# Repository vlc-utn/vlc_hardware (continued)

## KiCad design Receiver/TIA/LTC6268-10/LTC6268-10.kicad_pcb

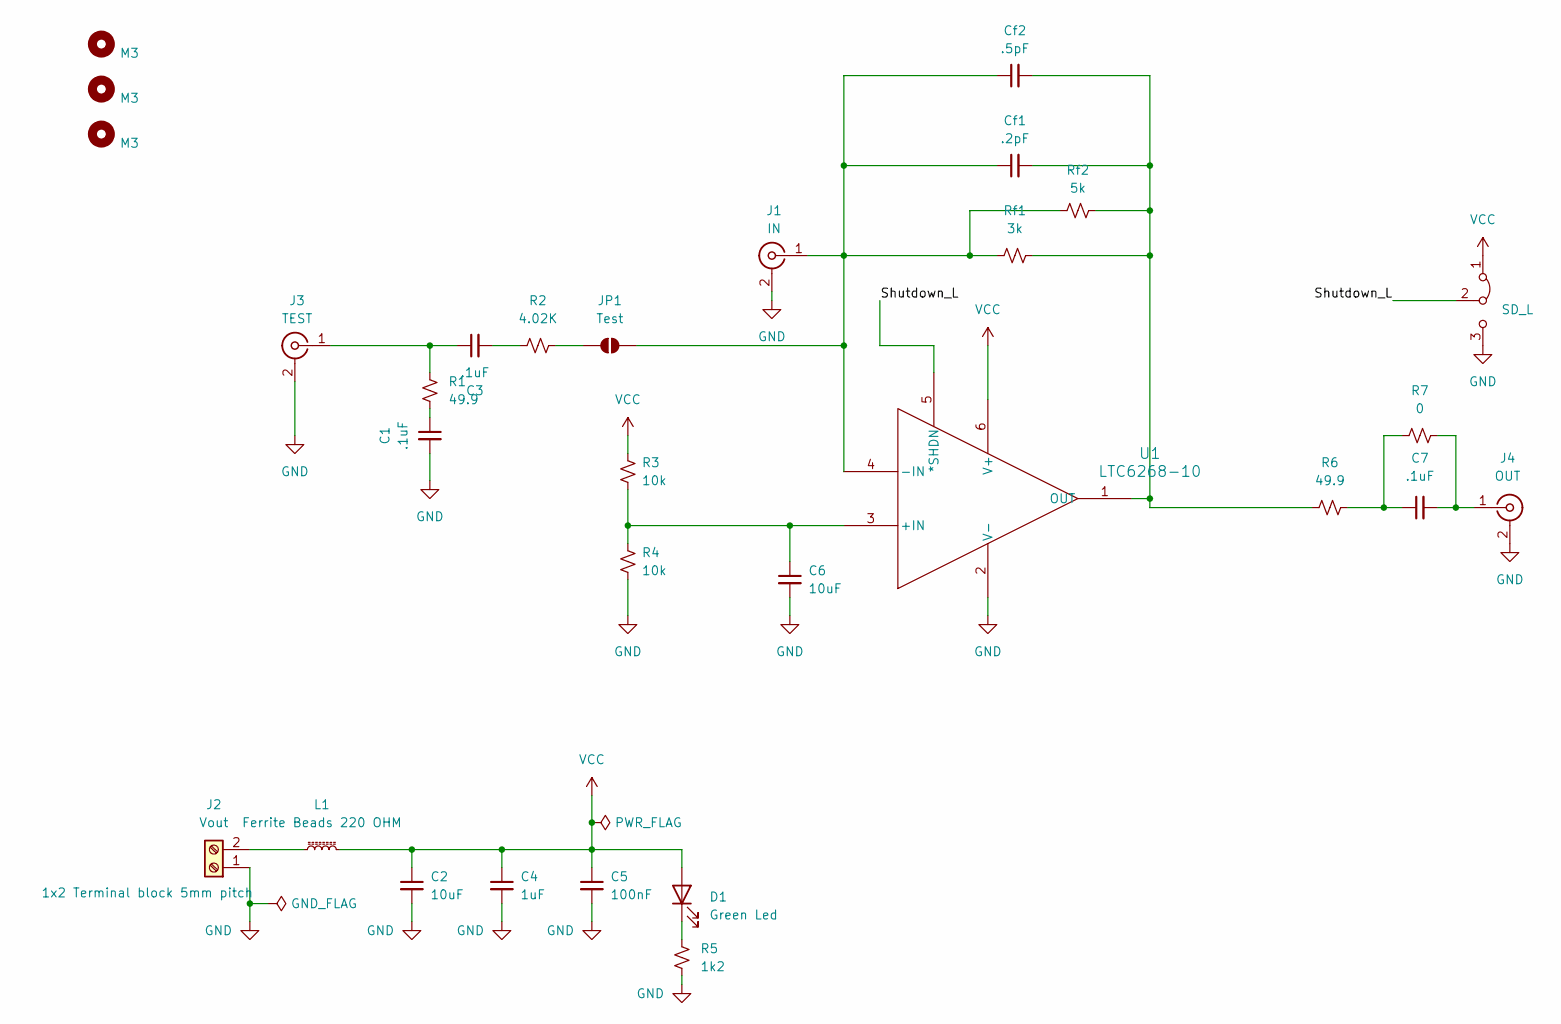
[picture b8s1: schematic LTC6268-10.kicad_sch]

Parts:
C1, C3, C7: .1uF; C_0402_1005Metric_Pad0.74x0.62mm_HandSolder; Manufacturer Part Number 530L104KT16; Mouser Part Number 581-530L104KT16
C2, C6: 10uF; C_0603_1608Metric_Pad1.08x0.95mm_HandSolder; Manufacturer Part Number GRM188Z71A106MA73D; Mouser Part Number 81-GRM188Z71A106MA3D
C4: 1uF; C_0603_1608Metric_Pad1.08x0.95mm_HandSolder; Manufacturer Part Number CL10B105KP8NNNC; Mouser Part Number 187-CL10B105KP8NNNC
C5: 100nF; C_0603_1608Metric_Pad1.08x0.95mm_HandSolder; Manufacturer Part Number CL10B104KO8NFNC; Mouser Part Number 187-CL10B104KO8NFNC
Cf1: .2pF; C_0402_1005Metric; Manufacturer Part Number 04023J0R2ZBSTR; Mouser Part Number 581-04023J0R2ZBSTR
Cf2: .5pF; C_0402_1005Metric; Manufacturer Part Number 04023J0R5BBSTR; Mouser Part Number 581-04023J0R5BBSTR
D1: Green Led; LED_0603_1608Metric; Manufacturer Part Number 150060VS75000; Mouser Part Number 710-150060VS75000
H1, H2, H3: M3; MountingHole_3.2mm_M3_DIN965
J1: IN; SMA_Samtec_SMA-J-P-X-ST-EM1_EdgeMount
J2: Vout; TerminalBlock_Phoenix_MKDS-1,5-2_1x02_P5.00mm_Horizontal
J3: TEST; SMA_Samtec_SMA-J-P-X-ST-EM1_EdgeMount
J4: OUT; SMA_Samtec_SMA-J-P-X-ST-EM1_EdgeMount
JP1: Test; R_0603_1608Metric_Pad0.98x0.95mm_HandSolder; Manufacturer Part Number MCT0603MZ0000ZP500; Mouser Part Number 594-MCT0603MZ0000ZP5
L1: Ferrite Beads 220 OHM; L_0603_1608Metric_Pad1.05x0.95mm_HandSolder; Manufacturer Part Number BLM18KG221SN1D; Mouser Part Number 81-BLM18KG221SN1D
R1, R6: 49.9; R_0603_1608Metric_Pad0.98x0.95mm_HandSolder; Manufacturer Part Number MCT06030C4999FP500; Mouser Part Number 594-MCT06030C4999FP5
R2: 4.02K; R_0603_1608Metric_Pad0.98x0.95mm_HandSolder; Manufacturer Part Number MCT06030C4021FP500; Mouser Part Number 594-MCT06030C4021FP5
R3, R4: 10k; R_0603_1608Metric_Pad0.98x0.95mm_HandSolder; Manufacturer Part Number CRCW060310K0FKEI; Mouser Part Number 71-CRCW060310K0FKEI
R5: 1k2; R_0603_1608Metric_Pad0.98x0.95mm_HandSolder; Manufacturer Part Number CRCW06031K20FKEA; Mouser Part Number 71-CRCW0603-1.2K-E3
R7: 0; R_0603_1608Metric_Pad0.98x0.95mm_HandSolder; Manufacturer Part Number MCT0603MZ0000ZP500; Mouser Part Number 594-MCT0603MZ0000ZP5
Rf1: 3k; R_0402_1005Metric; Manufacturer Part Number MCS04020D3001BE000; Mouser Part Number 594-MCS04020D3001BE0
Rf2: 5k; R_0402_1005Metric; Manufacturer Part Number MCS04020C4991FE000; Mouser Part Number 594-MCS04020C4991FE0
SD_L1: SD_L; PinHeader_1x03_P2.54mm_Vertical
U1: LTC6268-10; TSOT-23_S6_LIT; Manufacturer Part Number LTC6268IS6-10#TRMPBF; Mouser Part Number 584-C6268IS6-10TMPF

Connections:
/Shutdown_L: SD_L1.2 (C), U1.5 (*SHDN)
GND: C1.2, C2.2, C4.2, C5.2, C6.2, J1.2 (Ext), J2.1, J3.2 (Ext), J4.2 (Ext), R4.2, R5.2, SD_L1.3 (B), U1.2 (V-)
unnamed: C1.1, R1.2
unnamed: C3.2, R2.1
unnamed: C7.1, R6.2, R7.1
unnamed: D1.1 (K), R5.1
unnamed: Cf1.1, Cf2.1, J1.1 (In), JP1.2 (B), Rf1.1, Rf2.1, U1.4 (-IN)
unnamed: J2.2, L1.1
unnamed: C3.1, J3.1 (In), R1.1
unnamed: C7.2, J4.1 (In), R7.2
unnamed: JP1.1 (A), R2.2
unnamed: C6.1, R3.2, R4.1, U1.3 (+IN)
unnamed: Cf1.2, Cf2.2, R6.1, Rf1.2, Rf2.2, U1.1 (OUT)
VCC: C2.1, C4.1, C5.1, D1.2 (A), L1.2, R3.1, SD_L1.1 (A), U1.6 (V+)

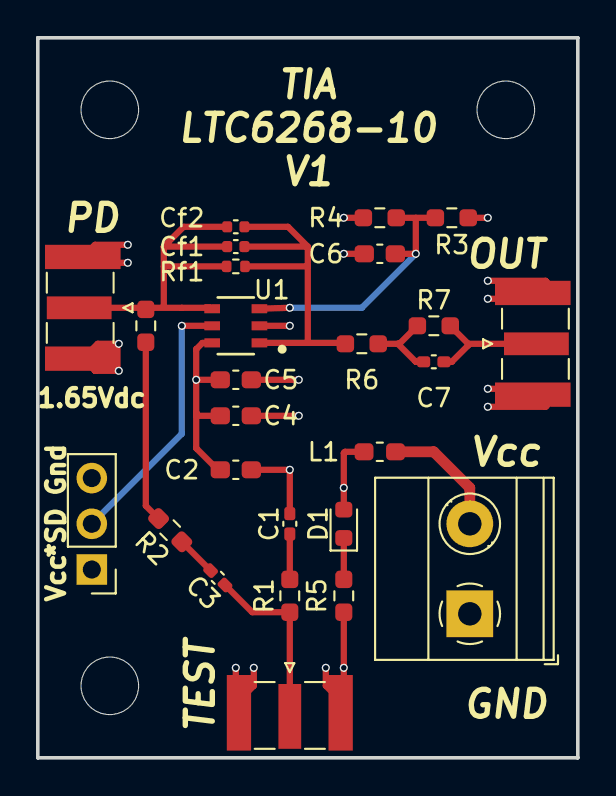
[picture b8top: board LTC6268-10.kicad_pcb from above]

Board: 4 copper layers, 30.0 x 40.0 mm, 29 parts (0 on the bottom side), 14 nets.

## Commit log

2025-01-05 Added folders for TIA and FCA
2025-01-05 Added repositories for TIA and FCA
    Added repositories for TIA and FCA
2025-01-05 Photodiode circuit
2025-01-06 Add preenfasis v1.0
2025-01-06 Preenfasis v1.1
    Se separaron los planos de tierra de ambas T
2025-01-07 Push v2 according to Issue#1
2025-01-07 Version Sma Edge
2025-01-07 tx amplifier v1.0
2025-01-07 add spice models
2025-01-07 v3 according to Issue #1
2025-01-08 Multiple updates
    SMA, Screw terminals, track widths, added some optional 0 ohm bypass resistors
2025-01-08 Small updates
2025-01-08 Small updates
    Update silkscreen font, height and weight
2025-01-08 LED uploaded, PD reworked
2025-01-08 PD reworked, LED uploaded
    PD reworked
2025-01-08 LED uploaded
2025-01-08 Some elements that were not uploaded and deleted
2025-01-09 Rx amp uploaded
2025-01-09 Fixed LED pcb
2025-01-09 LED corrections finished
2025-01-09 Updated jlcpcb constraints LED pcb
2025-01-09 v1.2 preenfasis
    Se cambia el tamaño de los tornillos de M2 a M3
2025-01-09 Last fix Led pcb
2025-01-09 Updated Rx Symbol Fields.
2025-01-09 tx amplifier v1.1
    Change M2 to M3 screws
2025-01-09 Updated FCA symbols
    Updated FCA symbols with mouser number parts.
2025-01-09 FCA DRC fix
    FCA DRC fix
2025-01-09 Capacitors descriptors fixed, some fix to DRC
    Capacitors descriptors fixed, some fix to DRC
2025-01-09 Checking Pre-Emphasis
    Checking Pre-Emphasis
2025-01-09 Added pre-emphasis to FCA simulation
    Added pre-emphasis filter to FCA simulation, you can connect and disconect filter at FCA input.
2025-01-10 Add CPW to preenfasis and tx amplifier
2025-01-10 Remove thermal relief and add clearance to MH of Preenfasis
2025-01-10 LMH34400 first versio
2025-01-10 LTC6268-10 first version
2025-01-10 LMH3440 fixed
    LMH3440 fixed
2025-01-10 FCA fixed
2025-01-10 Rx Amp first version
2025-01-10 Modified some thermal reliefs
2025-01-10 add clearance to MH of tx amplifier
2025-01-11 Fixed missing symbol LTC6268-10
2025-01-11 SMA footprint rx-amp fixed
    SMA footprint rx-amp fixed
2025-01-11 OPA2675 datasheet updated
    OPA2675 datasheet updated
2025-01-11 Thermal reliefes in LED pcb fixed
    Thermal reliefes in LED pcb fixed
2025-01-11 FCA simulation fixed.
    FCA simulation fixed. (PSPICE) full chain transmitter working.
2025-01-11 Receiver AMP updated ibom and gerber
    Receiver AMP updated ibom and gerber
2025-01-11 Updated ibom rx-amp. Output files for PD ok
    Updated ibom rx-amp. Output files for PD ok
2025-01-11 Gerbers and ibom for LMH34400 generated
    Gerbers and ibom for LMH34400 generated
2025-01-11 Gerbers and ibom LTC6268-10 generated
    Gerbers and ibom LTC6268-10 generated
2025-01-11 Gerbers and ibom Tx Amp generated
    Gerbers and ibom Tx Amp generated
2025-01-11 Gerbers and ibom generated TransmitterFCA
    Gerbers and ibom generated TransmitterFCA
2025-01-11 Gerbers and ibom generated LED pcb
    Gerbers and ibom generated LED pcb
2025-01-11 Gerbers and ibom pre pcb generated.
    Gerbers and ibom pre pcb generated
2025-01-11 Updated and fixed all gerbers. Created .zip for every board
    Updated and fixed all gerbers. Created .zip for every board
2025-01-11 Corrected some zip gerbers (not all)
    Corrected some zip gerbers (not all)
2025-01-11 Updated all zip folders from receiver.
    Updated all zip folders from receiver.
2025-01-11 Updeted gerbers from transmitter folders
    Updeted gerbers from transmitter folders
2025-02-11 Add vna measurements and schematic graphs
2025-07-29 english translation of plots
